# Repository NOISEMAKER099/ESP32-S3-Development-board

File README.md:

# ESP32-S3 Development Board

This repository documents a **personal ESP32-S3 based development board** designed for learning, experimentation, and embedded systems development.

---

## Table of Contents
1. [System Documentation](#system-documentation)
2. [Project Overview](#project-overview)
3. [Key Design Features](#key-design-features)
4. [Repository Structure](#repository-structure)
5. [Design Focus Areas](#design-focus-areas)
6. [Tools Used](#tools-used)
7. [Project Status](#project-status)
8. [Author](#author)

---

## System Documentation

- [Block Diagram Overview](docs/block_diagram_overview.md): High-level representation of the ESP32-S3 architecture.
- [Interface Overview](docs/interface_overview.md)
- [Power Architecture](docs/power_architecture.md)
- [Boot, Reset & Programming Flow](docs/boot_reset_programming.md): Details about programming workflows.
- [Board Visuals](docs/board_visuals.md)
- [Schematic Overview](hardware/schematics/schematic_overview.md)

### Board Images

---

## Project Overview

The ESP32-S3 Development Board is intended as a flexible platform for:
- Embedded systems learning and training.
- IoT and connectivity-based prototypes or experiments.
- Custom peripheral interfacing and hardware prototyping.

With USB-based programming, stable power regulation, and an accessible GPIO pin layout, the board is designed for development and ease of use.

---

## Key Design Features

- **ESP32-S3 microcontroller platform:**
  - Supporting Wi-Fi and Bluetooth connectivity for robust IoT development.
- **USB interface for versatile power and programming connectivity.**
- **Onboard voltage regulation (5 V to 3.3 V) ensures stable operation.**
- **Boot/reset circuits for efficient flashing and debugging workflows.**
- **Accessible GPIO support:**
  - UART, SPI, I²C, ADC, PWM interfaces.
  - Onboard status LED for development/debugging purposes.

---

## Repository Structure
- `docs/`: Documentation and architecture details.
- `hardware/`: Contains the board schematics and PCB artwork.
- `diagrams/`: Block and interface diagrams.
- `images/`: Photos and rendered views of the ESP32-S3 board.
- `README.md`: Main project documentation.

---

## Prerequisites

Before starting, ensure you have:
- A USB Type-C cable for board connectivity and flashing.
- [ESP-IDF Framework](https://github.com/espressif/esp-idf) or Arduino IDE installed on your computer.
- Python 3.6+ (required for ESP-IDF environment setup).
- [USB-to-Serial Driver](https://www.silabs.com/developers/usb-to-uart-bridge-vcp-drivers) (if required).

---

## Getting Started with the Development Board

### 1. Hardware Setup
- Connect the ESP32-S3 Development Board to your computer using a USB cable.
- Verify that the onboard status LED lights up when the board is powered.

### 2. Install ESP-IDF or Arduino
- Follow the [ESP-IDF Getting Started Guide](https://docs.espressif.com/projects/esp-idf/en/latest/esp32/get-started/).
- Alternatively, install the Arduino IDE.

### 3. Flashing Firmware
- Compile your code using `idf.py build` or Arduino IDE, and flash it to the board:
  ```bash
  idf.py flash

---

## Pin Layout

| GPIO Pin | Function              | Notes                          |
|----------|-----------------------|--------------------------------|
| GPIO0    | Boot and Reset Button | Used for programming and reset |
| GPIO1    | TXD (UART TX)         | Serial communication (output)  |
| GPIO3    | RXD (UART RX)         | Serial communication (input)   |
| GPIO4    | GPIO                  | General-purpose I/O pin        |
| GPIO38   | GPIO with Pull-up     | Supports embedded pull-up      |
| GPIO21   | GPIO for SK6812 LED   | Drives onboard RGB LED         |
| GPIO5    | Digital GPIO          | General-purpose output pin     |

---

### Additional Notes:
1. **Power Pins:**
   - **VCC_3V3**: Supplies regulated 3.3V power to the ESP32-S3 and peripherals.
   - **GND**: Ground connection points throughout the design.

2. **USB Pins:**
   - **USB_DM (D-)** and **USB_DP (D+)**: USB signal routing for programming and communication.
   - **VBUS**: Detects USB power supply (5V).

3. **Special Features:**
   - **GPIO21**: Directly connected to the onboard RGB LED (SK6812), useful for indicating status or debugging output.
   - **GPIO0**: Dual-use pin for boot mode selection and reset.
  
   ---

## Design Focus Areas

Key aspects of the design include:
1. Power Supply and Regulation strategy.
2. Boot Configuration and Reset Logic.
3. GPIO Layout for versatility and ease of use.
4. USB Signal Routing and Connectivity.
5. **Hardware Reliability** through layout planning.

---

## Tools Used

The following tools were used during development:
- [KiCad](https://www.kicad.org/): Design and layout of schematics/PCBs.
- [ESP-IDF](https://github.com/espressif/esp-idf): Development framework.
- Arduino (planned firmware compatibility).

---

## Disclaimer

This is a **personal hardware project** for educational purposes.  
**Not intended for commercial or safety-critical applications.** Use at your own risk.

---

## Contribution Guidelines

Contributions are welcome! If you notice any issues or want to improve the design/documentation:
1. Fork this repository.
2. Create a feature branch for your improvements.
3. Open a pull request with a description of changes.

For major updates, open an issue to discuss the feature or improvement!

---

## License

This project is licensed under the MIT License. See the [LICENSE](LICENSE) file for details.

---

## Future Enhancements

- Firmware examples for common IoT applications.
- Expandable GPIO breakouts for additional peripherals.
- Battery-powered operation (optional add-on board).
- 3D-printed enclosure designs.

---

## Project Status

This project is **functionally complete**. Further updates, if added, will aim at incremental improvements or enhancements for learning purposes.

---

## Author

Smit Gaikwad  
Electronics & Telecommunication Engineer

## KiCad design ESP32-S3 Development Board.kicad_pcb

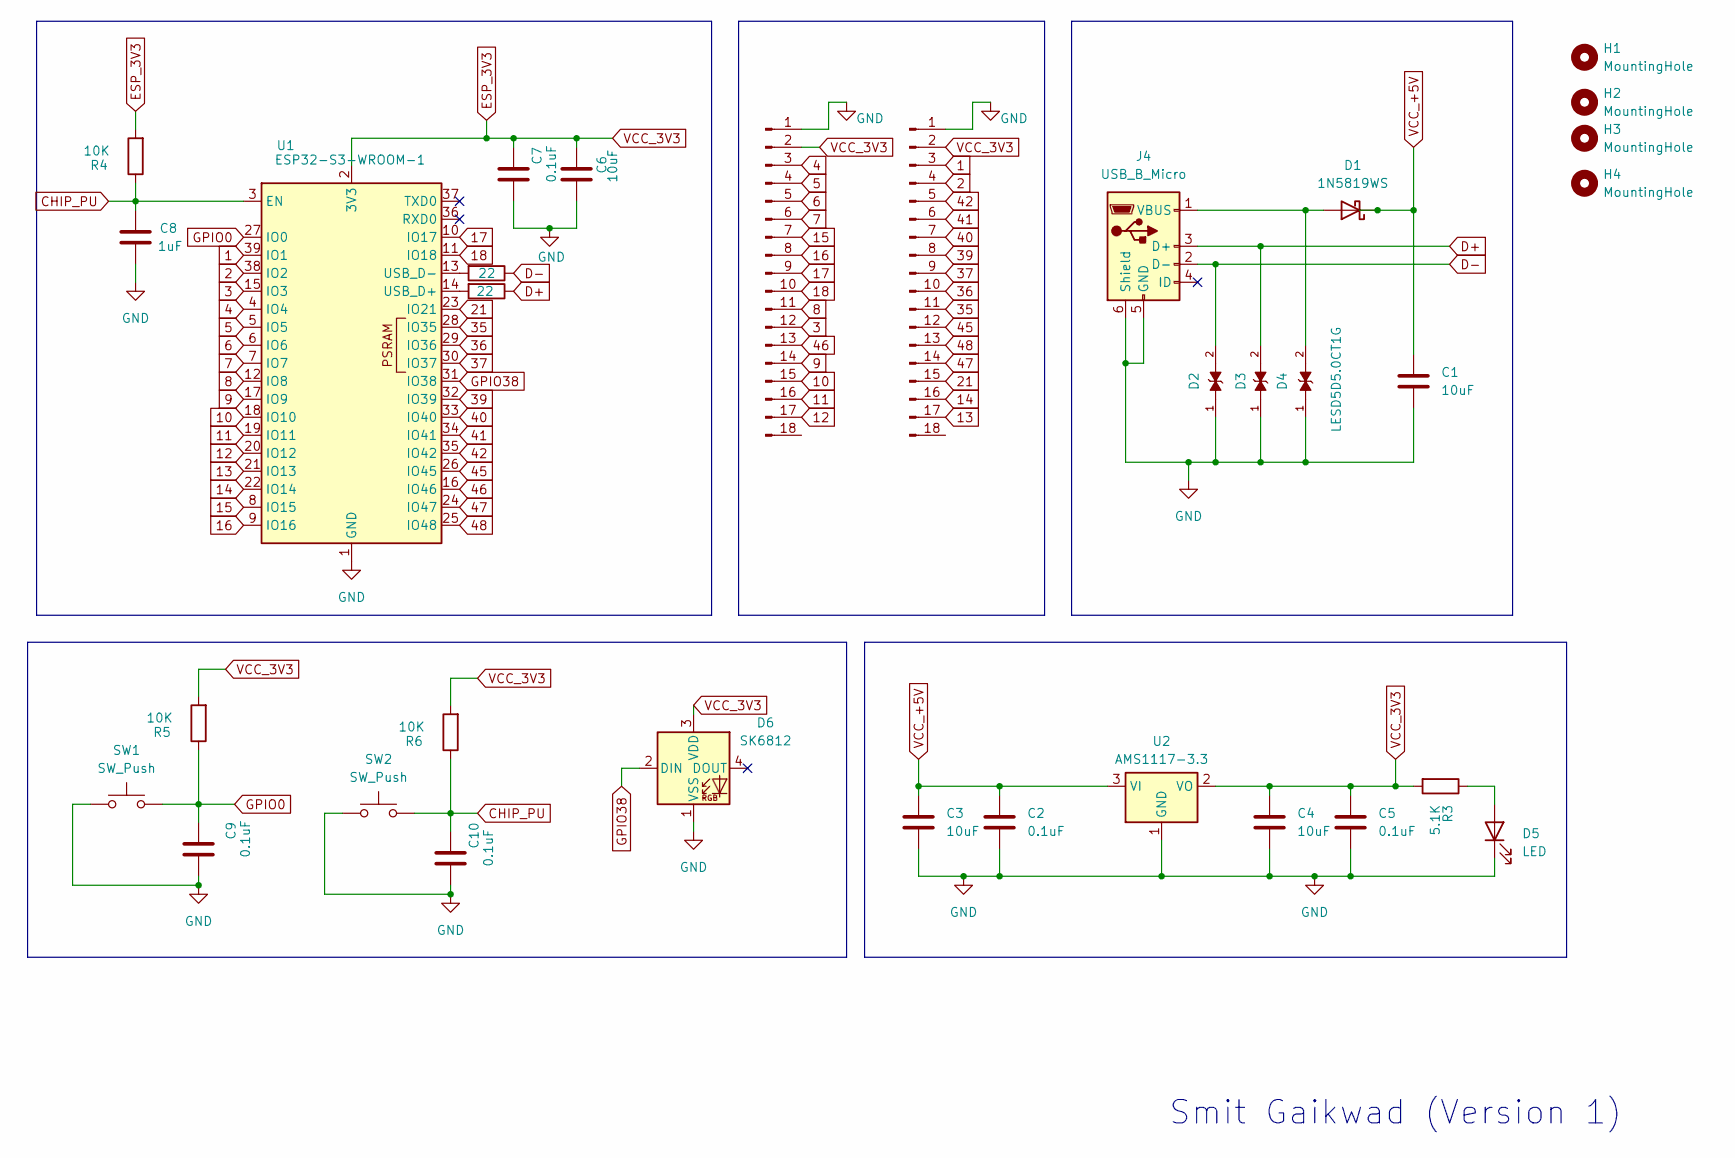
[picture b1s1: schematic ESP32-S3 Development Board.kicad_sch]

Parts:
C1, C3, C4, C6: 10uF; C_0805_2012Metric_Pad1.18x1.45mm_HandSolder
C2, C5, C7, C9, C10: 0.1uF; C_0805_2012Metric_Pad1.18x1.45mm_HandSolder
C8: 1uF; C_0805_2012Metric_Pad1.18x1.45mm_HandSolder
D1: 1N5819WS; D_SOD-323
D2, D3, D4: LESD5D5.0CT1G
D5: LED; LED_0805_2012Metric_Pad1.15x1.40mm_HandSolder
D6: SK6812; LED_SK6812_PLCC4_5.0x5.0mm_P3.2mm
H1, H2, H3, H4: MountingHole; MountingHole_2.1mm
J1, J2: Conn_01x18_Pin; PinHeader_1x18_P2.54mm_Vertical
J4: USB_B_Micro; USB_Micro-B_Molex_47346-0001
R3: 5.1K; R_0805_2012Metric_Pad1.20x1.40mm_HandSolder
R4, R5, R6: 10K; R_0805_2012Metric_Pad1.20x1.40mm_HandSolder
R7, R8: 22; R_0402_1005Metric_Pad0.72x0.64mm_HandSolder
SW1, SW2: SW_Push; SW_Push_SPST_NO_Alps_SKRK
U1: ESP32-S3-WROOM-1
U2: AMS1117-3.3; SOT-223-3_TabPin2

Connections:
1: J2.3, U1.39 (IO1)
2: J2.4, U1.38 (IO2)
3: J1.12, U1.15 (IO3)
4: J1.3, U1.4 (IO4)
5: J1.4, U1.5 (IO5)
6: J1.5, U1.6 (IO6)
7: J1.6, U1.7 (IO7)
8: J1.11, U1.12 (IO8)
9: J1.14, U1.17 (IO9)
10: J1.15, U1.18 (IO10)
11: J1.16, U1.19 (IO11)
12: J1.17, U1.20 (IO12)
13: J2.17, U1.21 (IO13)
14: J2.16, U1.22 (IO14)
15: J1.7, U1.8 (IO15)
16: J1.8, U1.9 (IO16)
17: J1.9, U1.10 (IO17)
18: J1.10, U1.11 (IO18)
21: J2.15, U1.23 (IO21)
35: J2.11, U1.28 (IO35)
36: J2.10, U1.29 (IO36)
37: J2.9, U1.30 (IO37)
39: J2.8, U1.32 (IO39)
40: J2.7, U1.33 (IO40)
41: J2.6, U1.34 (IO41)
42: J2.5, U1.35 (IO42)
45: J2.12, U1.26 (IO45)
46: J1.13, U1.16 (IO46)
47: J2.14, U1.24 (IO47)
48: J2.13, U1.25 (IO48)
CHIP_PU: C8.1, C10.1, R4.1, R6.1, SW2.2, U1.3 (EN)
D+: D3.2, J4.3 (D+), R7.1
D-: D2.2, J4.2 (D-), R8.1
ESP_3V3: C4.1, C5.1, C6.1, C7.1, D6.3 (VDD), J1.2, J2.2, R3.2, R4.2, R5.2, R6.2, U1.2 (3V3), U2.2 (VO)
GND: C1.2, C2.2, C3.2, C4.2, C5.2, C6.2, C7.2, C8.2, C9.2, C10.2, D2.1, D3.1, D4.1, D5.1 (K), D6.1 (VSS), J1.1, J2.1, J4.5 (GND), J4.6 (Shield), SW1.1, SW2.1, U1.1 (GND), U1.40 (GND), U1.41 (GND), U2.1 (GND)
GPIO0: C9.1, R5.1, SW1.2, U1.27 (IO0)
GPIO38: D6.2 (DIN), U1.31 (IO38)
unnamed: D1.2 (A), D4.2, J4.1 (VBUS)
unnamed: D5.2 (A), R3.1
unnamed: R7.2, U1.14 (USB_D+)
unnamed: R8.2, U1.13 (USB_D-)
VCC_+5V: C1.1, C2.1, C3.1, D1.1 (K), U2.3 (VI)

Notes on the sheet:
Smit Gaikwad (Version 1)

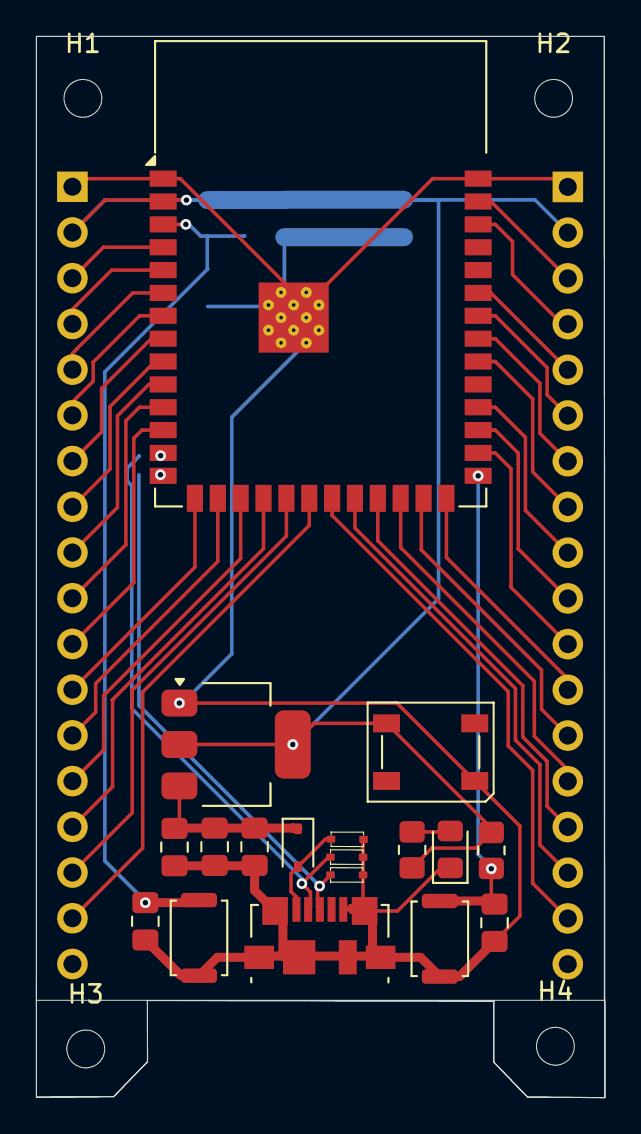
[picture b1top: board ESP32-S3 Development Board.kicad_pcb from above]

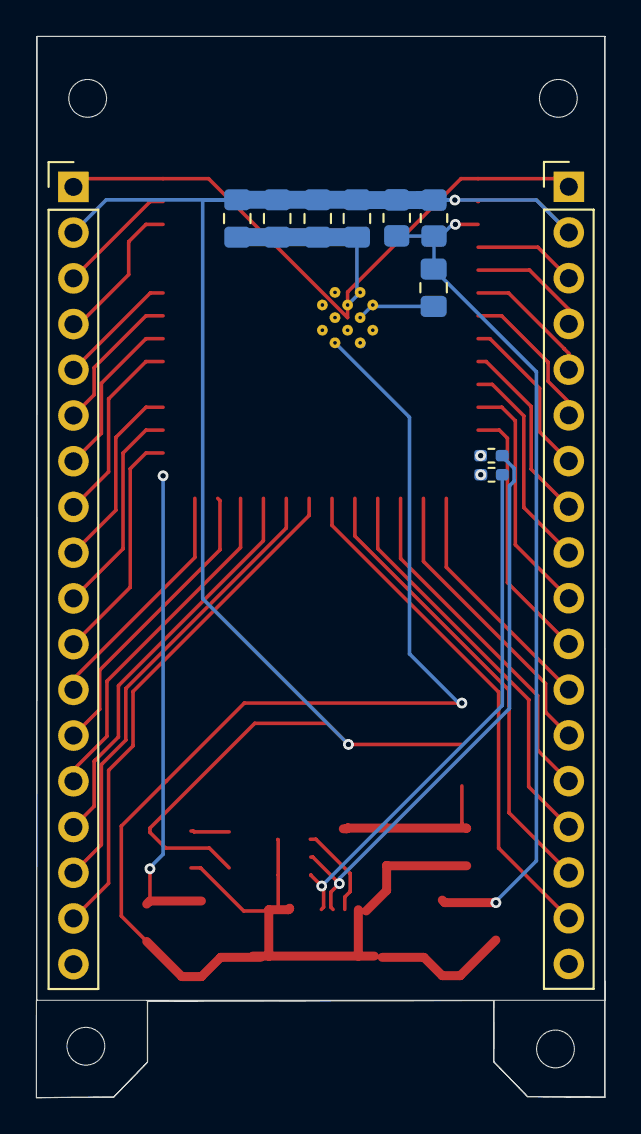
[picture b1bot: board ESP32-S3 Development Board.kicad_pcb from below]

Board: 2 copper layers, 31.6 x 59.0 mm, 33 parts (11 on the bottom side), 42 nets.

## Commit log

2025-12-17 Create docs folder
2025-12-17 Create diagrams folder
2025-12-17 Rewrite README with documentation-first structure
2025-12-17 Add block diagram overview documentation
2025-12-17 Link ESP32-S3 block diagram and documentation
2025-12-17 Add ESP32-S3 system block diagram
2025-12-17 Add ESP32-S3 interface overview documentation
2025-12-17 Link interface overview documentation
2025-12-17 Add power architecture documentation
2025-12-17 Link power architecture documentation
2025-12-17 Add boot, reset, and programming flow documentation
2025-12-17 Link boot and programming documentation
2025-12-17 Add ESP32-S3 board images
2025-12-17 Add board visuals documentation
2025-12-17 Link board visuals in README
2025-12-17 Create schematics folder
2025-12-17 Add schematics README
2025-12-17 Add KiCad schematic files for ESP32-S3 development board
2025-12-17 Add schematic block-level overview documentation
2025-12-17 Link schematic overview documentation
2025-12-17 Mark project as functionally complete
2025-12-17 Revise README for clarity and organization
    Updated README.md for improved clarity and structure.
2025-12-17 Enhance README with setup and contribution details
    Added prerequisites, getting started guide, contribution guidelines, and future enhancements sections to the README.
